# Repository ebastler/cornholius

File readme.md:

# Cornholius Keyboard

Cornholius is, first and foremost, a Bluetooth Low Energy capable replacement PCB for the [Foostan Cornelius](https://github.com/foostan/corneliuskbd). Key and connector positions as well as PCB outline and plate were derived from the original Cornelius repository, but altered to fit the scope of this project - Thank you for open sourcing these files! In accordance with the license chosen by foostan, this project was published under the same license: <a href="http://creativecommons.org/licenses/by-nc-sa/4.0/?ref=chooser-v1" target="_blank" rel="license noopener noreferrer" style="display:inline-block;">CC BY-NC-SA 4.0</a>.

Parts of this project:
* [PCB](./hotswap_ble/) [100%]
* [Plate](./plate_ble/) [100%]
* 3D printable cornelius/cornholius PCB compatible case [100%] - Published on [Printables](https://www.printables.com/model/1543214-cornholius-keyboard-case)

## Cornholius PCB
The PCB is designed to be 100% assemblable by jlcpcb in their "economic" PCBA option (without hotswap sockets), or the more expensive "standard" PCBA option incl. hotswap sockets. It uses an [Ebyte nRF52840_E73-2G4M08S1C](https://www.ebyte.com/en/downpdf.aspx?id=445) BLE module, which is part of their component library, so no external components must be ordered from other shops. This module is configured for full 2-stage DC-DC operation in high voltage mode for maximum battery life.

Battery management is handled by a [TI BQ24075](http://www.ti.com/lit/ds/symlink/bq24075.pdf) battery management/power path IC, with a charge current of approx. 440 mA and all relevant protections in place. The PCB is designed for a HAC-006 (Nintendo Switch Joycon) battery, as replacement cells for it are affordable and easy to source, and are plug and play for Cornholius, incl. the right connector. It should lead to an estimated battery life of up to 8 months (according to ZMK power profiler).

If you want to use any other battery type, make sure it has a Molex Pico EZmate 2-pin connector, and the correct polarity. Connecting a battery with mismatched polarity may damage the PCB and can potentially turn into a fire hazard.

The 6th column on the PCB can be snapped off, turning it into a 5col PCB.

### Programming
Flashing an nRF52840 forn the first time requires hardware tools. Joric wrote up a very good guide on how to program nRF52 series chips in the [nrfmicro github wiki](https://github.com/joric/nrfmicro/wiki/Bootloader). If you have never flashed a nRF52 series chip before, I suggest reading it before proceeding to order any hardware.

The PCB features a TC2030 flashing header footprint, configured in [TC2030-CTX-NL](https://www.tag-connect.com/wp-content/uploads/bsk-pdf-manager/TC2030-CTX_1.pdf) pinout. It should be possible to solder wires to this footprint and connect to a debug probe, but I have not tried. 

Precompiled bootloader files can be found in the Github Actions tab of my [fork of the Adafruit nRF52 Bootloader](https://github.com/ebastler/Adafruit_nRF52_Bootloader/actions).

Once the PCBs have a bootloader, they can be programmed via a UF2 mass-storage-device bootloader. Double-tapping the reset button (or using keybinds, once ZMK is running) will send the device to bootloader. 

### Ordering
Gerber files and assembly files can be found in the [hotswap_ble/fab subfolder](./hotswap_ble/fab/). Use 1.6mm FR4 substrate.

The jlcpcb assembly files are tested and were working at the time when I ordered prototypes, however, jlcpcb sometimes changes part numbers, or parts run out of stock and need to be replaced by new parts. Please proceed with caution and carefully check both BOM and position/alignment/orientation of all components when uploading to their site.

## Cornholius Plate
The plate is made from FR4 substrate, without any copper plating, to minimie interference with the antenna. It also has a hole above the PCB's status LED to keep it visible. While it is compatible with Cornelius cases, the outline and the gasket tabs were slightly altered from the original Cornelius plate to allow for o-ring mount in Cornholius.

### Ordering
Gerber files and assembly files can be found in the [plate_ble/fab subfolder](./plate_ble/fab/). Use 1.6mm FR4 substrate.

## Cornholius Case
For more information regarding the case and necessary mounting hardware, visit my [Printables](https://www.printables.com/model/1543214-cornholius-keyboard-case) page. All files were published there, as well as a list of hardware needed for the assembly. The case will need a Cornholius plate for the o-ring mounting, regular Cornelius plates might fit but are untested.

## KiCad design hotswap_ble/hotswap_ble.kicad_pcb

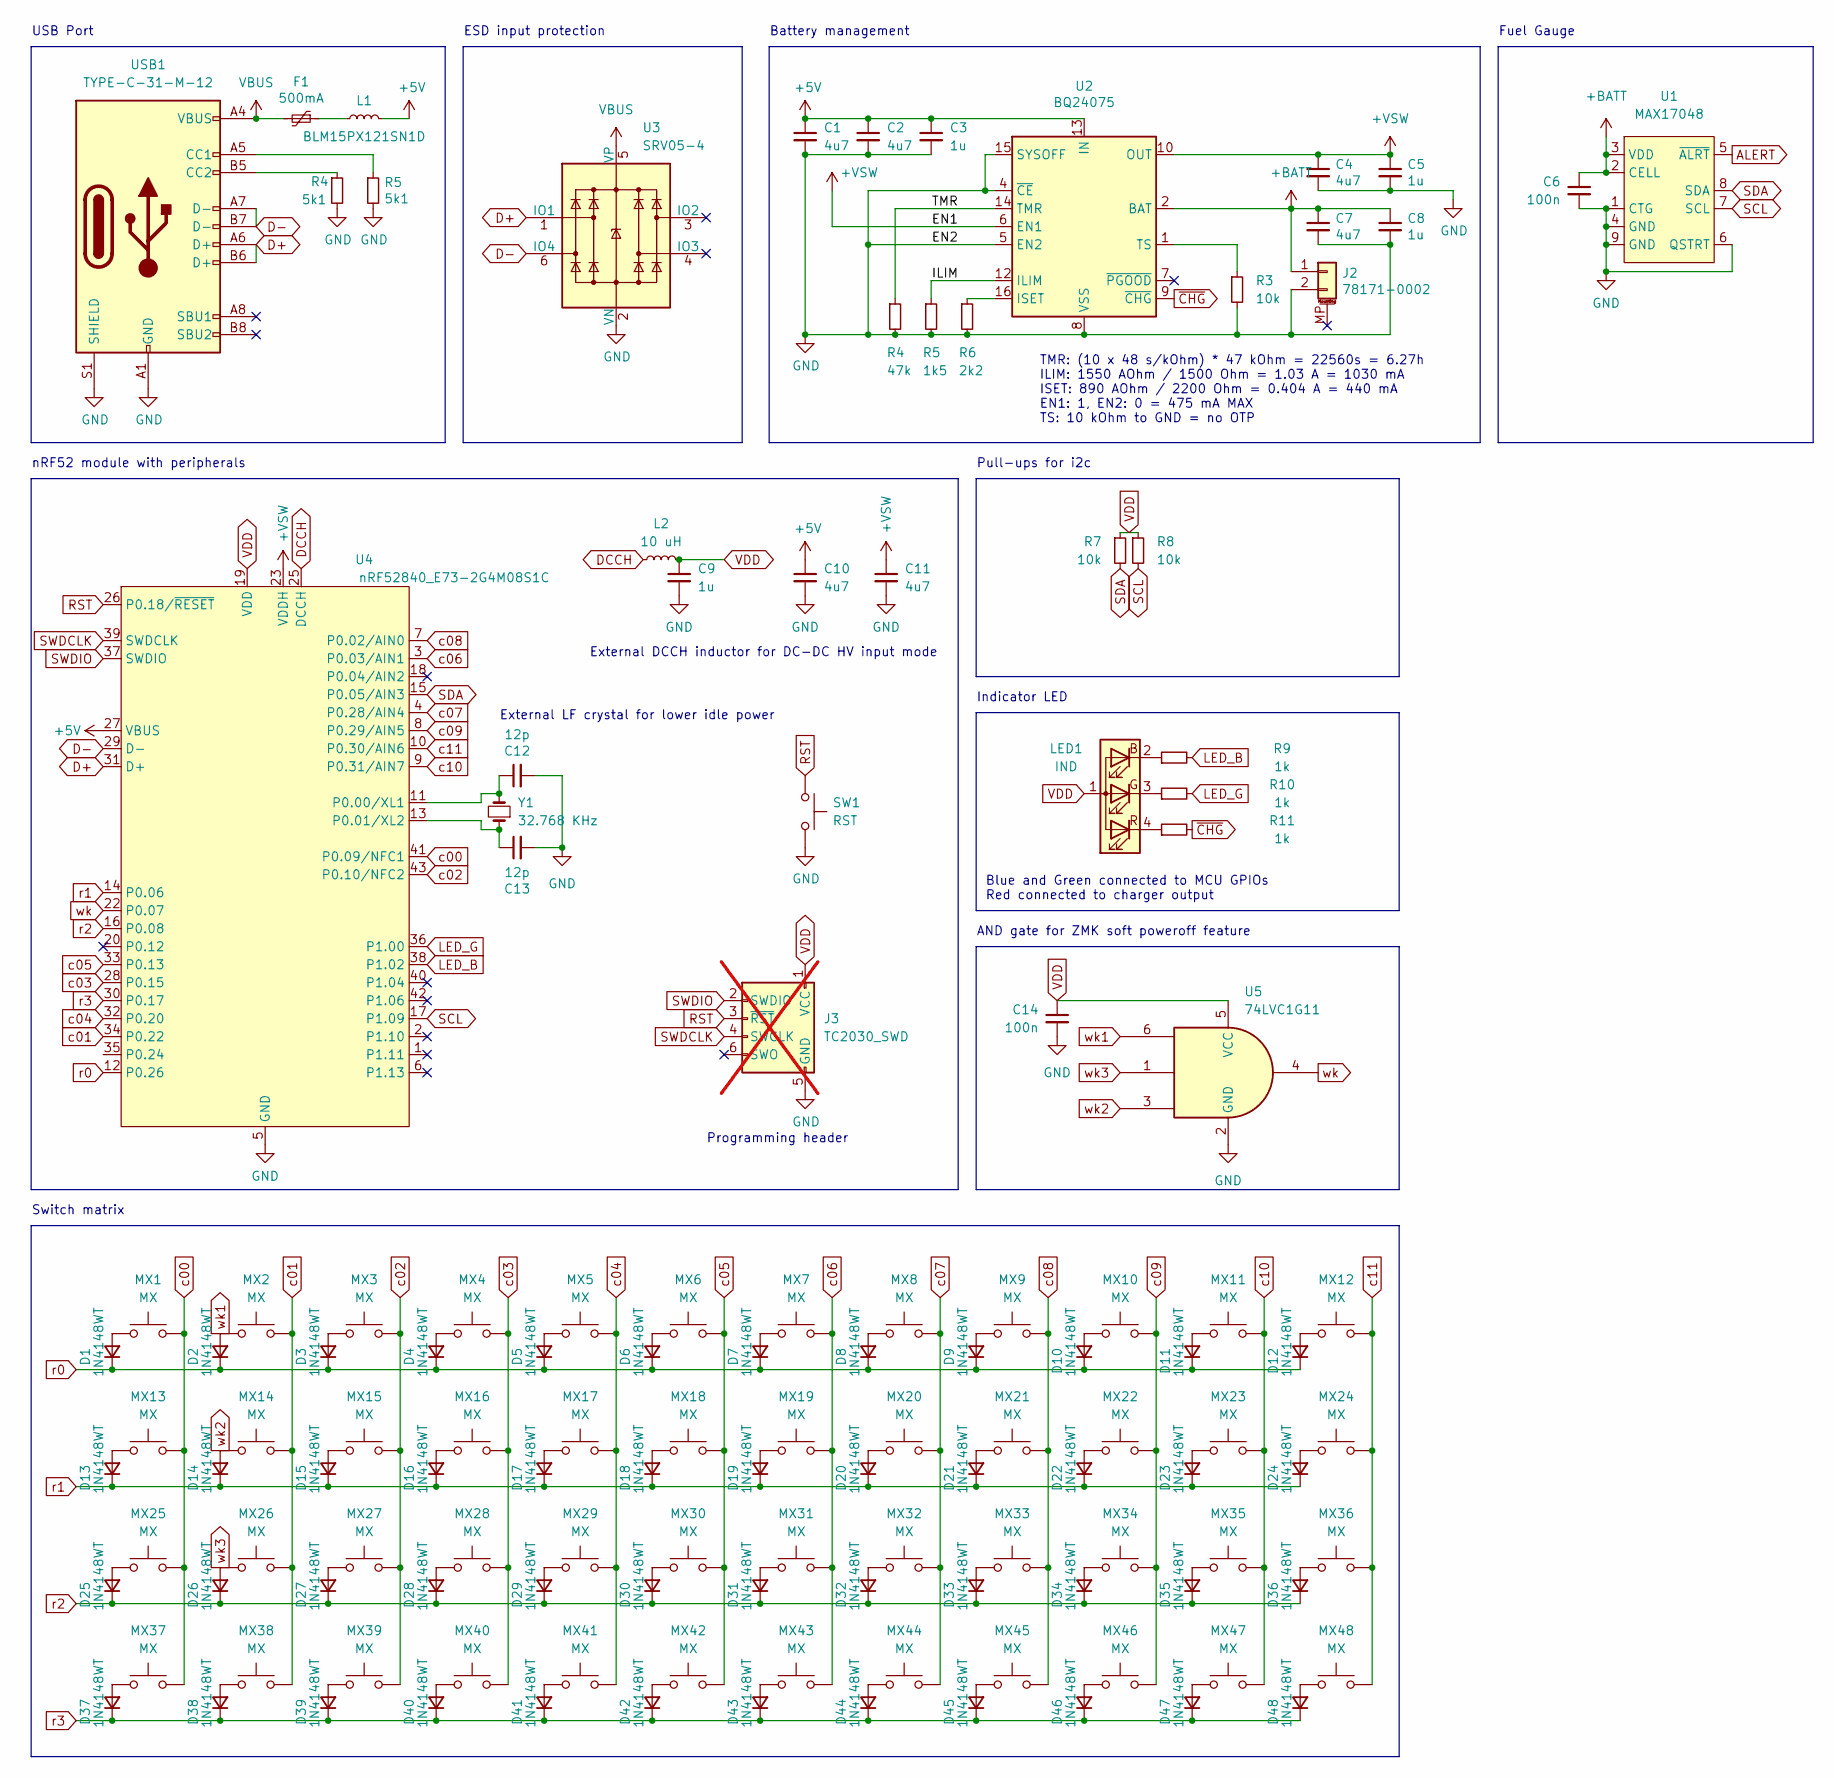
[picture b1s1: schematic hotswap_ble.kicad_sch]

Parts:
C1, C2, C4, C7, C10, C11: 4u7; C_0402_1005Metric; LCSC C23733
C3, C5, C8, C9: 1u; C_0402_1005Metric; LCSC C52923
C6, C14: 100n; C_0402_1005Metric; LCSC C307331
C12, C13: 12p; C_0402_1005Metric; LCSC C1547
D1, D2, D3, D4, D5, D6, D7, D8, D9, D10, D11, D12, D13, D14, D15, D16, D17, D18, D19, D20, D21, D22, D23, D24, D25, D26, D27, D28, D29, D30, D31, D32, D33, D34, D35, D36, D37, D38, D39, D40, D41, D42, D43, D44, D45, D46, D47, D48: 1N4148WT; D_SOD-523; LCSC C727112
F1: 500mA; Fuse_0603_1608Metric; LCSC C883095
J2: 78171-0002; Molex_Pico-EZmate_78171-0002_1x02-1MP_P1.20mm_Vertical; LCSC C505023
J3: TC2030_SWD; CON_TC2030_outlined; not fitted
L1: BLM15PX121SN1D; L_0402_1005Metric; LCSC C88970
L2: 10 uH; L_0603_1608Metric; LCSC C92982
LED1: IND; LED_1206R; LCSC C2802677
MX1, MX2, MX3, MX4, MX5, MX6, MX7, MX8, MX9, MX10, MX11, MX12, MX13, MX14, MX15, MX16, MX17, MX18, MX19, MX20, MX21, MX22, MX23, MX24, MX25, MX26, MX27, MX28, MX29, MX30, MX31, MX32, MX33, MX34, MX35, MX36, MX37, MX38, MX39, MX40, MX41, MX42, MX43, MX44, MX45, MX46, MX47, MX48: MX; SW_MX_HS_1u; LCSC C5184526
R3, R7, R8: 10k; R_0402_1005Metric; LCSC C25744
R4: 47k; R_0402_1005Metric; LCSC C25792
R5: 5k1; R_0402_1005Metric; LCSC C25905
R6: 2k2; R_0402_1005Metric; LCSC C25879
R9, R10, R11: 1k; R_0402_1005Metric; LCSC C11702
SW1: RST; SW_T1A2QR; LCSC C100056
U1: MAX17048; DFN-8-1EP_2x2mm_P0.5mm_EP0.7x1.3mm; LCSC C2682616
U2: BQ24075; VQFN-16-1EP_3x3mm_P0.5mm_EP1.6x1.6mm; LCSC C15464
U3: SRV05-4; SOT-23-6-routable; LCSC C7420376
U4: nRF52840_E73-2G4M08S1C; LCSC C356849
U5: 74LVC1G11; SOT-363_SC-70-6
USB1: TYPE-C-31-M-12; USB_C_Receptacle_HRO_TYPE-C-31-M-12; LCSC C165948
Y1: 32.768 KHz; Crystal_SMD_2012-2Pin_2.0x1.2mm; LCSC C55208

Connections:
+5V: C1.1, C2.1, C3.1, C10.1, L1.2, U2.13 (IN), U4.27 (VBUS)
+BATT: C6.1, C7.1, C8.1, J2.1, U1.2 (CELL), U1.3 (VDD), U2.2 (BAT), U2.3 (BAT)
+VSW: C4.1, C5.1, C11.1, U2.6 (EN1), U2.10 (OUT), U2.11 (OUT), U4.23 (VDDH)
ALERT: U1.5 (~ALRT)
D+: U3.1 (IO1), U4.31 (D+); also elsewhere on the board
D-: U3.6 (IO4), U4.29 (D-); also elsewhere on the board
DCCH: L2.1, U4.25 (DCCH)
GND: C1.2, C2.2, C3.2, C4.2, C5.2, C6.2, C7.2, C8.2, C9.2, C10.2, C11.2, C12.2, C13.2, C14.2, J2.2, J3.5 (GND), R3.2, R4.2, R5.2, R6.2, SW1.2, U1.1 (CTG), U1.4 (GND), U1.6 (QSTRT), U1.9 (GND), U2.4 (~CE), U2.5 (EN2), U2.8 (VSS), U2.15 (SYSOFF), U2.17 (VSS), U3.2 (VN), U4.5 (GND), U4.21 (GND), U4.24 (GND), U5.2 (GND); also elsewhere on the board
LED_B: R9.2, U4.38 (P1.02)
LED_G: R10.2, U4.36 (P1.00)
unnamed: D1.2 (A), MX1.1
unnamed: D3.2 (A), MX3.1
unnamed: D4.2 (A), MX4.1
unnamed: D5.2 (A), MX5.1
unnamed: D6.2 (A), MX6.1
unnamed: D7.2 (A), MX7.1
unnamed: D8.2 (A), MX8.1
unnamed: D9.2 (A), MX9.1
unnamed: D10.2 (A), MX10.1
unnamed: D11.2 (A), MX11.1
unnamed: D12.2 (A), MX12.1
unnamed: D13.2 (A), MX13.1
unnamed: D15.2 (A), MX15.1
unnamed: D16.2 (A), MX16.1
unnamed: D17.2 (A), MX17.1
unnamed: D18.2 (A), MX18.1
unnamed: D19.2 (A), MX19.1
unnamed: D20.2 (A), MX20.1
unnamed: D21.2 (A), MX21.1
unnamed: D22.2 (A), MX22.1
unnamed: D23.2 (A), MX23.1
unnamed: D24.2 (A), MX24.1
unnamed: D25.2 (A), MX25.1
unnamed: D27.2 (A), MX27.1
unnamed: D28.2 (A), MX28.1
unnamed: D29.2 (A), MX29.1
unnamed: D30.2 (A), MX30.1
unnamed: D31.2 (A), MX31.1
unnamed: D32.2 (A), MX32.1
unnamed: D33.2 (A), MX33.1
unnamed: D34.2 (A), MX34.1
unnamed: D35.2 (A), MX35.1
unnamed: D36.2 (A), MX36.1
unnamed: D37.2 (A), MX37.1
unnamed: D38.2 (A), MX38.1
unnamed: D39.2 (A), MX39.1
unnamed: D40.2 (A), MX40.1
unnamed: D41.2 (A), MX41.1
unnamed: D42.2 (A), MX42.1
unnamed: D43.2 (A), MX43.1
unnamed: D44.2 (A), MX44.1
unnamed: D45.2 (A), MX45.1
unnamed: D46.2 (A), MX46.1
unnamed: D47.2 (A), MX47.1
unnamed: D48.2 (A), MX48.1
unnamed: F1.1, L1.1
unnamed: LED1.2 (BK), R9.1
unnamed: LED1.3 (GK), R10.1
unnamed: LED1.4 (RK), R11.1
unnamed: R6.1, U2.16 (ISET)
unnamed: R3.1, U2.1 (TS)
unnamed: C12.1, U4.11 (P0.00/XL1), Y1.2
unnamed: C13.1, U4.13 (P0.01/XL2), Y1.1
RST: J3.3 (~RST), SW1.1, U4.26 (P0.18/~RESET)
SCL: R8.2, U1.7 (SCL), U4.17 (P1.09)
SDA: R7.2, U1.8 (SDA), U4.15 (P0.05/AIN3)
SWDCLK: J3.4 (SWCLK), U4.39 (SWDCLK)
SWDIO: J3.2 (SWDIO), U4.37 (SWDIO)
VBUS: F1.2, U3.5 (VP); also elsewhere on the board
VDD: C9.1, C14.1, J3.1 (VCC), L2.2, LED1.1 (A), R7.1, R8.1, U4.19 (VDD), U5.5 (VCC)
c00: MX1.2, MX13.2, MX25.2, MX37.2, U4.41 (P0.09/NFC1)
c01: MX2.2, MX14.2, MX26.2, MX38.2, U4.34 (P0.22)
c02: MX3.2, MX15.2, MX27.2, MX39.2, U4.43 (P0.10/NFC2)
c03: MX4.2, MX16.2, MX28.2, MX40.2, U4.28 (P0.15)
c04: MX5.2, MX17.2, MX29.2, MX41.2, U4.32 (P0.20)
c05: MX6.2, MX18.2, MX30.2, MX42.2, U4.33 (P0.13)
c06: MX7.2, MX19.2, MX31.2, MX43.2, U4.3 (P0.03/AIN1)
c07: MX8.2, MX20.2, MX32.2, MX44.2, U4.4 (P0.28/AIN4)
c08: MX9.2, MX21.2, MX33.2, MX45.2, U4.7 (P0.02/AIN0)
c09: MX10.2, MX22.2, MX34.2, MX46.2, U4.8 (P0.29/AIN5)
c10: MX11.2, MX23.2, MX35.2, MX47.2, U4.9 (P0.31/AIN7)
c11: MX12.2, MX24.2, MX36.2, MX48.2, U4.10 (P0.30/AIN6)
r0: D1.1 (K), D2.1 (K), D3.1 (K), D4.1 (K), D5.1 (K), D6.1 (K), D7.1 (K), D8.1 (K), D9.1 (K), D10.1 (K), D11.1 (K), D12.1 (K), U4.12 (P0.26)
r1: D13.1 (K), D14.1 (K), D15.1 (K), D16.1 (K), D17.1 (K), D18.1 (K), D19.1 (K), D20.1 (K), D21.1 (K), D22.1 (K), D23.1 (K), D24.1 (K), U4.14 (P0.06)
r2: D25.1 (K), D26.1 (K), D27.1 (K), D28.1 (K), D29.1 (K), D30.1 (K), D31.1 (K), D32.1 (K), D33.1 (K), D34.1 (K), D35.1 (K), D36.1 (K), U4.16 (P0.08)
r3: D37.1 (K), D38.1 (K), D39.1 (K), D40.1 (K), D41.1 (K), D42.1 (K), D43.1 (K), D44.1 (K), D45.1 (K), D46.1 (K), D47.1 (K), D48.1 (K), U4.30 (P0.17)
wk: U4.22 (P0.07), U5.4
wk1: D2.2 (A), MX2.1, U5.6
wk2: D14.2 (A), MX14.1, U5.3
wk3: D26.2 (A), MX26.1, U5.1
~CHG: R11.2, U2.9 (~CHG)

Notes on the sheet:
nRF52 module with peripherals
Fuel Gauge
Indicator LED
AND gate for ZMK soft poweroff feature
Programming header
External LF crystal for lower idle power
USB Port
ESD input protection
TMR: (10 x 48 s/kOhm) * 47 kOhm = 22560s = 6.27h ILIM: 1550 AOhm / 1500 Ohm = 1.03 A = 1030 mA ISET: 890 AOhm / 2200 Ohm = 0.404 A = 440 mA EN1: 1, EN2: 0 = 475 mA MAX TS: 10 kOhm to GND = no OTP
External DCCH inductor for DC-DC HV input mode
Pull-ups for i2c
Battery management
Switch matrix
Blue and Green connected to MCU GPIOs Red connected to charger output

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
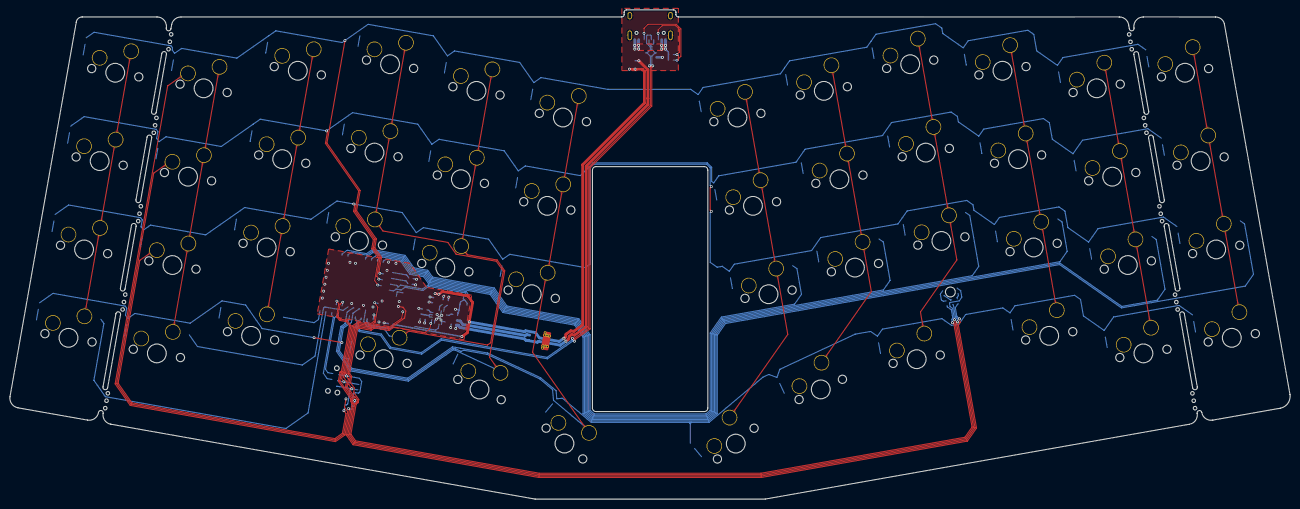
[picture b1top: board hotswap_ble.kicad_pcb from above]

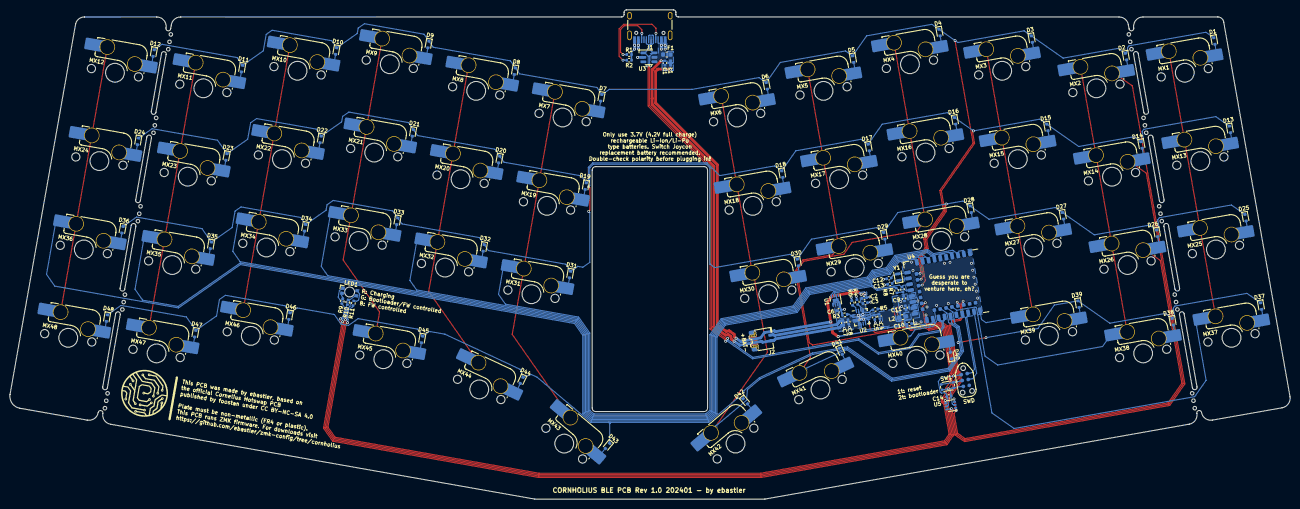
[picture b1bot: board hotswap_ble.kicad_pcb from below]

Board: 2 copper layers, 271.8 x 103.9 mm, 135 parts (135 on the bottom side), 94 nets.

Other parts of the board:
J1: TYPE-C-31-M-12; USB_C_Receptacle_HRO_TYPE-C-31-M-12
R1, R2: 5k1; R_0402_1005Metric

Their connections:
D+: J1.A6 (D+), J1.B6 (D+); also elsewhere on the board
D-: J1.A7 (D-), J1.B7 (D-); also elsewhere on the board
GND: J1.A1 (GND), J1.A12 (GND), J1.B1 (GND), J1.B12 (GND), J1.S1 (SHIELD), R1.2, R2.2; also elsewhere on the board
VBUS: J1.A4 (VBUS), J1.A9 (VBUS), J1.B4 (VBUS), J1.B9 (VBUS); also elsewhere on the board

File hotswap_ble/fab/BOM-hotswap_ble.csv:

Comment,Designator,Footprint,LCSC
RST,SW1,SW_T1A2QR,C100056
1k,"R10,R11,R9",R_0402_1005Metric,C11702
BQ24075,U2,VQFN-16-1EP_3x3mm_P0.5mm_EP1.6x1.6mm,C15464
12p,"C12,C13",C_0402_1005Metric,C1547
TYPE-C-31-M-12,J1,USB_C_Receptacle_HRO_TYPE-C-31-M-12,C165948
4u7,"C1,C10,C11,C2,C4,C7",C_0402_1005Metric,C23733
10k,"R3,R7,R8",R_0402_1005Metric,C25744
47k,R4,R_0402_1005Metric,C25792
1k5,R5,R_0402_1005Metric,C25867
2k2,R6,R_0402_1005Metric,C25879
5k1,"R1,R2",R_0402_1005Metric,C25905
MAX17048,U1,DFN-8-1EP_2x2mm_P0.5mm_EP0.7x1.3mm,C2682616
IND,LED1,LED_1206R,C2802677
100n,"C14,C6",C_0402_1005Metric,C307331
nRF52840_E73-2G4M08S1C,U4,nRF52840_E73-2G4M08S1C,C356849
74LVC1G11,U5,SOT-363_SC-70-6,C460525
78171-0002,J2,Molex_Pico-EZmate_78171-0002_1x02-1MP_P1.20mm_Vertical,C505023
MX,"MX1,MX10,MX11,MX12,MX13,MX14,MX15,MX16,MX17,MX18,MX19,MX2,MX20,MX21,MX22,MX23,MX24,MX25,MX26,MX27,MX28,MX29,MX3,MX30,MX31,MX32,MX33,MX34,MX35,MX36,MX37,MX38,MX39,MX4,MX40,MX41,MX42,MX43,MX44,MX45,MX46,MX47,MX48,MX5,MX6,MX7,MX8,MX9",SW_MX_HS_1u,C5184526
1u,"C3,C5,C8,C9",C_0402_1005Metric,C52923
32.768 KHz,Y1,Crystal_SMD_2012-2Pin_2.0x1.2mm,C55208
1N4148WT,"D1,D10,D11,D12,D13,D14,D15,D16,D17,D18,D19,D2,D20,D21,D22,D23,D24,D25,D26,D27,D28,D29,D3,D30,D31,D32,D33,D34,D35,D36,D37,D38,D39,D4,D40,D41,D42,D43,D44,D45,D46,D47,D48,D5,D6,D7,D8,D9",D_SOD-523,C727112
SRV05-4,U3,SOT-23-6-routable,C7420376
500mA,F1,Fuse_0603_1608Metric,C883095
BLM15PX121SN1D,L1,L_0402_1005Metric,C88970
10 uH,L2,L_0603_1608Metric,C92982

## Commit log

2024-02-18 add gitignore for kicad projects
2024-02-18 add license
2024-02-18 add readme
2024-02-18 add pcb and plate files
2024-02-18 remove libs from lib tables that were used by foostan but not by me
2024-02-18 Update readme.md
    add license link to readme
2024-02-18 Improve license link
2026-01-05 Update readme.md
    Add links and info regarding 3d printed case

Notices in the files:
hotswap_ble/hotswap_ble.kicad_pcb:
published by foostan under CC BY-NC-SA 4.0
